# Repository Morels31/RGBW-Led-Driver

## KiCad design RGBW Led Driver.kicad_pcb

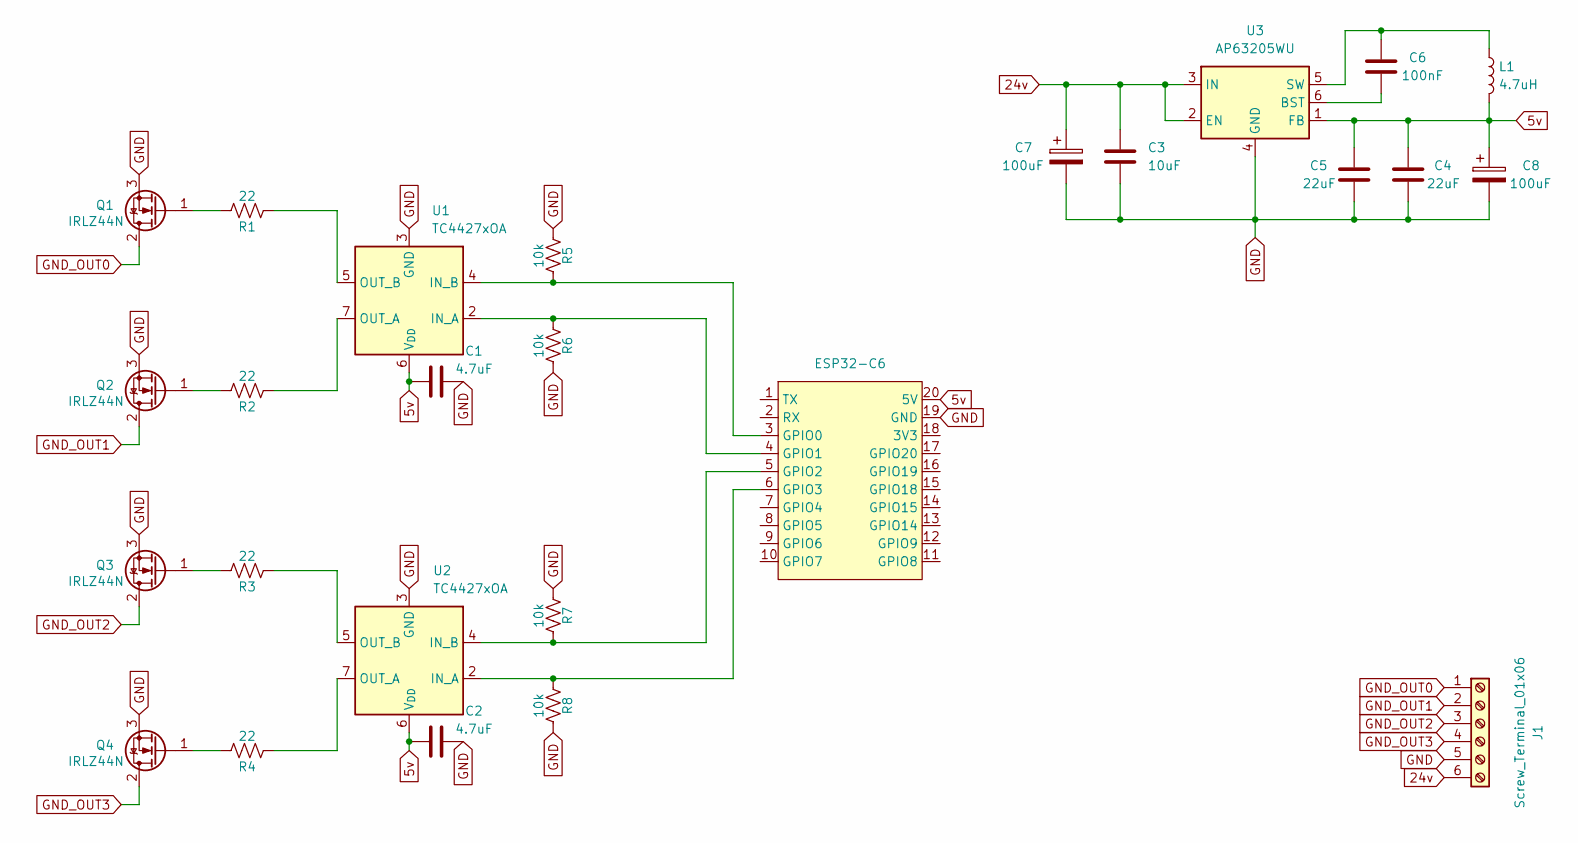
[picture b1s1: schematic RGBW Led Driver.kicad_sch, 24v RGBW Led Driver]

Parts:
C1, C2: 4.7uF; C_1206_3216Metric_Pad1.33x1.80mm_HandSolder
C3: 10uF; C_1206_3216Metric_Pad1.33x1.80mm_HandSolder
C4, C5: 22uF; C_1206_3216Metric_Pad1.33x1.80mm_HandSolder
C6: 100nF; C_1206_3216Metric_Pad1.33x1.80mm_HandSolder
C7: 100uF; CP_Radial_D6.3mm_P2.50mm
C8: 100uF; CP_Radial_D5.0mm_P2.50mm
D1: ESP32-C6; ESP32-C6 Supermini
J1: Screw_Terminal_01x06; TerminalBlock_Phoenix_MKDS-1,5-6-5.08_1x06_P5.08mm_Horizont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
L1: 4.7uH; CDRH127
Q1, Q2, Q3, Q4: IRLZ44N; TO-220-3_Vertical
R1, R2, R3, R4: 22; R_0805_2012Metric_Pad1.20x1.40mm_HandSolder
R5, R6, R7, R8: 10k; R_0805_2012Metric_Pad1.20x1.40mm_HandSolder
U1, U2: TC4427xOA; SOIC-8_3.9x4.9mm_P1.27mm
U3: AP63205WU; TSOT-23-6

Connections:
5v: C1.1, C2.1, C4.2, C5.2, C8.1, D1.20 (5V), L1.2, U1.6 (V_{DD}), U2.6 (V_{DD}), U3.1 (FB)
24v: C3.1, C7.1, J1.6, U3.2 (EN), U3.3 (IN)
GND: C1.2, C2.2, C3.2, C4.1, C5.1, C7.2, C8.2, D1.19 (GND), J1.5, Q1.3 (S), Q2.3 (S), Q3.3 (S), Q4.3 (S), R5.2, R6.2, R7.2, R8.2, U1.3 (GND), U2.3 (GND), U3.4 (GND)
GND_OUT0: J1.1, Q1.2 (D)
GND_OUT1: J1.2, Q2.2 (D)
GND_OUT2: J1.3, Q3.2 (D)
GND_OUT3: J1.4, Q4.2 (D)
unnamed: D1.3 (GPIO0), R5.1, U1.4 (IN_B)
unnamed: D1.4 (GPIO1), R6.1, U1.2 (IN_A)
unnamed: D1.5 (GPIO2), R7.1, U2.4 (IN_B)
unnamed: D1.6 (GPIO3), R8.1, U2.2 (IN_A)
unnamed: Q1.1 (G), R1.2
unnamed: Q2.1 (G), R2.2
unnamed: Q3.1 (G), R3.2
unnamed: Q4.1 (G), R4.2
unnamed: R2.1, U1.7 (OUT_A)
unnamed: R1.1, U1.5 (OUT_B)
unnamed: R4.1, U2.7 (OUT_A)
unnamed: R3.1, U2.5 (OUT_B)
unnamed: C6.2, U3.6 (BST)
unnamed: C6.1, L1.1, U3.5 (SW)

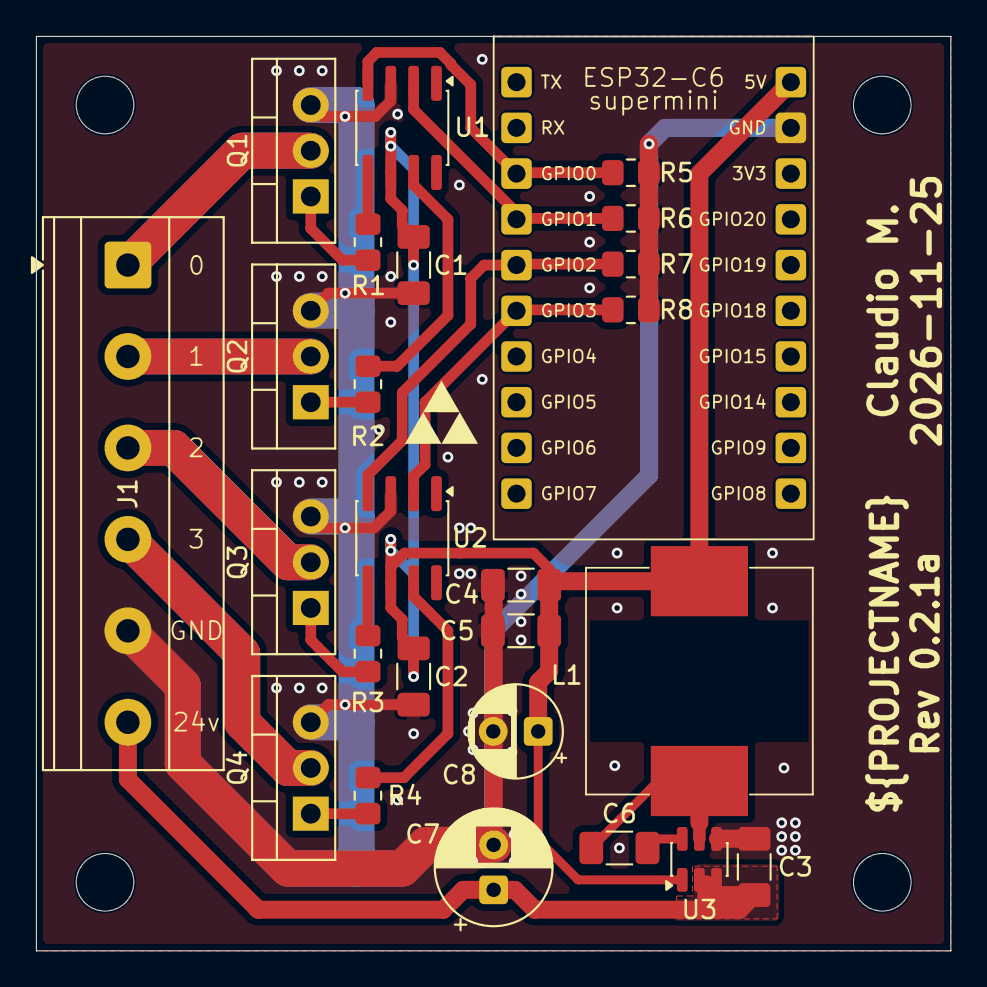
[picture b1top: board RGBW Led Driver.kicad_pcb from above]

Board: 2 copper layers, 50.8 x 50.8 mm, 26 parts (0 on the bottom side), 21 nets.
